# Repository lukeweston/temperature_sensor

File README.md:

# temperature_sensor

Quick, simple 10µA bias for Lakeshore DT-670 temperature sensor

Expected diode voltage 1.5785V at 4.2K

(Helium head temperature will depend on compression, in closed-loop cryocooler.)

A precision benchtop voltmeter is preferred for voltage readout.

Temperature range 1.4K - 420K (500K for some, depends on Lakeshore packaging type)

Lakeshore temperature lookup table:

https://www.lakeshore.com/products/categories/specification/temperature-products/cryogenic-temperature-sensors/dt-670-silicon-diodes

{}

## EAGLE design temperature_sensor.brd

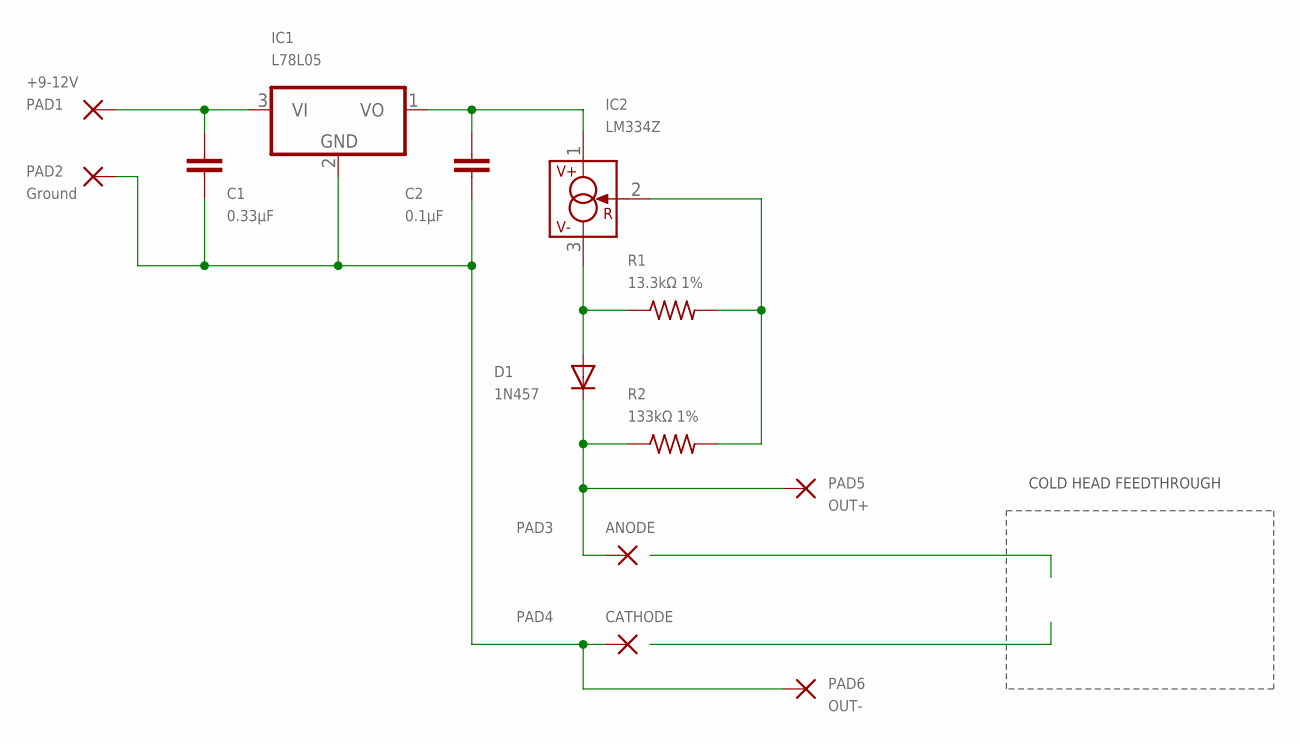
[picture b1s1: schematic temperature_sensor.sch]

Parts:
C1: 0.33µF; C050-024X044
C2: 0.1µF; C050-024X044
D1: 1N457; DO41-10
IC1: L78L05; TO92
IC2: LM334Z; TO92
PAD1: +9-12V; 2,54/1,0
PAD2: Ground; 2,54/1,0
PAD3: ANODE; 2,54/1,0
PAD4: CATHODE; 2,54/1,0
PAD5: OUT+; 2,54/1,0
PAD6: OUT-; 2,54/1,0
R1: 13.3kΩ 1%; 0207/10
R2: 133kΩ 1%; 0207/10

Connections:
GND: C1.2, C2.2, IC1.2 (GND), PAD2.1, PAD4.1, PAD6.1
unnamed: C1.1, IC1.3 (VI), PAD1.1
unnamed: C2.1, IC1.1 (VO), IC2.1 (V+)
unnamed: D1.C, PAD3.1, PAD5.1, R2.1
unnamed: D1.A, IC2.3 (V-), R1.1
unnamed: IC2.2 (R), R1.2, R2.2

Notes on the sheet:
COLD HEAD FEEDTHROUGH

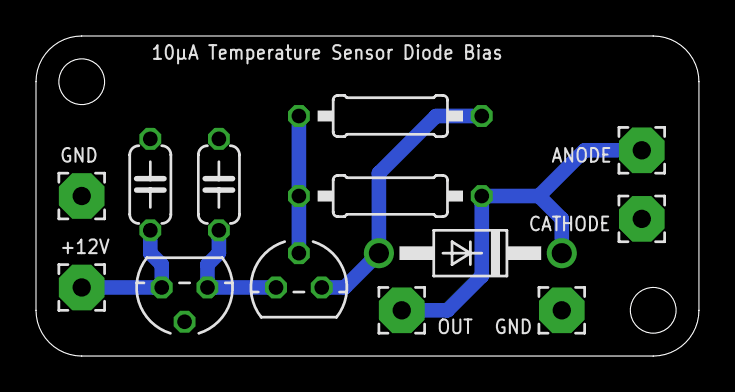
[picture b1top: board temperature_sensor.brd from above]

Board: 2 copper layers, 36.8 x 17.8 mm, 13 parts (0 on the bottom side), 6 nets.

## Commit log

2019-06-09 readme
2019-06-09 added gerber files
